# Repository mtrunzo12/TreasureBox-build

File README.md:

# Knock-to-Unlock Treasure Chest

Build a toy chest with a saved knock rhythm, keypad PIN, servo claw, lights and music. This folder is a curated snapshot of Mark and Liam's build. Start small: get the inputs working on a breadboard before ordering boards.

## Start here

1. Install [Claude Code](https://code.claude.com/docs/en/setup) or [Codex](https://developers.openai.com/codex/quickstart/), plus [Arduino IDE](https://www.arduino.cc/en/software/) and [KiCad](https://www.kicad.org/download/).
2. Download and unzip this build kit. Open the whole `treasure-chest` folder in your AI coding app. From [GitHub](https://github.com/mtrunzo12/TreasureBox-build), use Code → Download ZIP; no terminal or Git knowledge is required. Forking is optional and gives you your own place to save changes.
3. Paste the prompt from `START-HERE.md`. Ask the assistant to explain the next small step, then stop for your measurements or a photo. Do not ask it to order parts or fabricate a board before the checks below.

## What is included

- `firmware/treasure_box/`: current v8.5 sketch and its two required headers. Keep all three files in this folder.
- `firmware/USER_MANUAL.md`: using the toy and recording knock/PIN/music settings.
- `firmware/DEVELOPER.md`: exact pin map, dependencies, programming workflow and mechanical limits.
- `treasure_box_main/`: main-board schematic, layout, KiCad project and original exported BOM.
- `treasure_box_frontpanel/`: panel-board schematic, layout, KiCad project and original exported BOM.
- Each board folder includes the historical A0 Gerber/drill package and individual fabrication files.
- `PARTS.csv`: combined exported PCB component lists (44 placements across both boards). These are design values/footprints, not a verified supplier cart. The off-board parts are listed below.
- `KNOWN-ISSUES.md`: read this before spending money.
- `CHECKLIST.md`: a build sequence for a parent and child.
- `SOURCE-MANIFEST.json`: snapshot and source hashes. No family photographs, device backups, EEPROM dumps, credentials, local history or old build logs are included.

## Ordering the boards

This is the as-built A0 design, not a newly reviewed production release. The owner reports a backwards USB-C design; the build uses a removable ATmega328P programmed in a compatible DIP Uno. Resolve and review that issue before treating this as a plug-in USB design.

1. Open the `.kicad_pro` in each board folder. Check component orientation, connector pin numbering, footprint fit, board outline and hole locations against your parts and chest.
2. Run KiCad's electrical and PCB design-rule checks. Review their findings; a clean result alone does not prove the connector or physical wiring is correct.
3. Decide whether you are intentionally reproducing A0 with the Uno programming workaround or correcting the hardware first. If changed, regenerate Gerber and drill files from that exact saved revision. Do not order the historical ZIP for a revised board.
4. Upload **one ZIP per board** to JLCPCB. Confirm both copper layers, masks, silkscreen, board outline, drill holes and displayed dimensions in the preview. Use the [JLCPCB KiCad export guide](https://jlcpcb.com/help/article/how-to-generate-gerber-and-drill-files-in-kicad-9).
5. Choose bare PCB fabrication if you want to solder it yourselves. This package is not a turnkey assembly order; it does not include verified supplier part numbers or placement data. Check quantity, material, thickness and finish against the actual design before paying.
6. Check the delivered bare boards for obvious defects and shorts before populating them.

## Off-board parts to plan for

A wooden chest; piezo knock disc; reed switch and magnet; tilt switch; 4×4 keypad; passive speaker; illuminated arm button; red, green and blue lights with the appropriate wiring/resistors; four-AA holder and cells; main power switch; matching 16-way ribbon connectors/cable; keypad harness; wire, mounting hardware and strain relief. The installed claw is ServoCity 3219-0002-0002 with a goBILDA Proton Torque 2002-0180-0002 servo. Verify all electrical ratings and connector pitches before buying.

Tools: soldering iron, solder, ventilation, wire cutters/strippers, multimeter, breadboard/jumpers, and a compatible socketed ATmega328P Uno for the documented programming workaround. An adult handles soldering and initial powered claw tests. Keep fingers clear of the mechanism.

## Firmware

Open `firmware/treasure_box/treasure_box.ino` in Arduino IDE. The documented target is Arduino Uno / ATmega328P, Arduino AVR Boards 1.8.8 and Servo 1.3.0. Use the developer guide for the correct `BENCH_WIRING` choice; the custom PCB uses `false`, even when its removable chip is programmed in an Uno. Review the actual pin map before loading it onto a different breadboard arrangement.

An unprogrammed ATmega328P may need its bootloader and fuse configuration prepared first. Do not assume every purchased chip arrives Uno-ready. Power everything off before transferring a socketed chip, and check its notch orientation.

The code was built and tested on the original setup. Knock sensitivity, mechanical endpoints, wake behavior and battery draw still need testing on your own assembled chest. This is a toy latch, not a security lock.

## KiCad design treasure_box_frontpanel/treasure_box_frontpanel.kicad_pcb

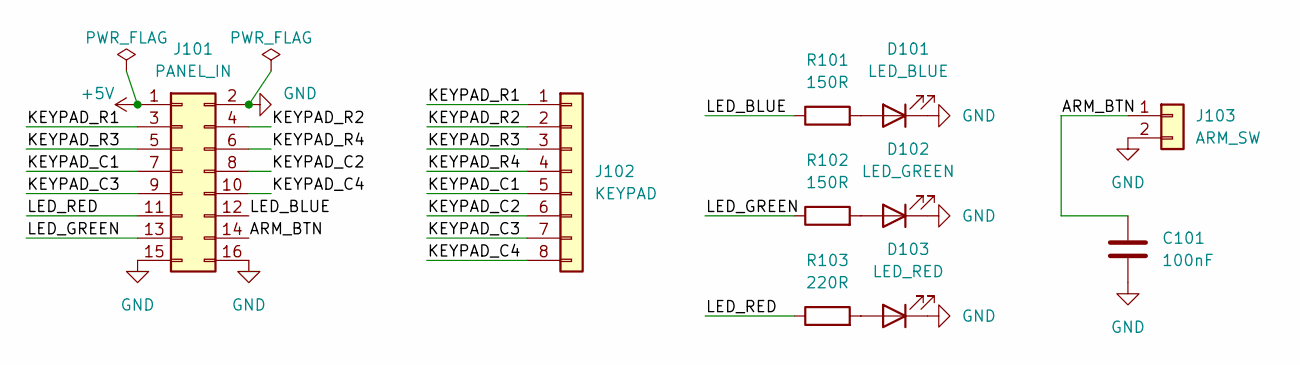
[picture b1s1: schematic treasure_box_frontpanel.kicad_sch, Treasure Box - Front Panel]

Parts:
C101: 100nF; C_Disc_D5.0mm_W2.5mm_P5.00mm
D101: LED_BLUE; TerminalBlock_MaiXu_MX126-5.0-02P_1x02_P5.00mm
D102: LED_GREEN; TerminalBlock_MaiXu_MX126-5.0-02P_1x02_P5.00mm
D103: LED_RED; TerminalBlock_MaiXu_MX126-5.0-02P_1x02_P5.00mm
J101: PANEL_IN; IDC-Header_2x08_P2.54mm_Vertical
J102: KEYPAD; JST_XH_B8B-XH-A_1x08_P2.50mm_Vertical
J103: ARM_SW; TerminalBlock_MaiXu_MX126-5.0-02P_1x02_P5.00mm
R101, R102: 150R; R_Axial_DIN0207_L6.3mm_D2.5mm_P10.16mm_Horizontal
R103: 220R; R_Axial_DIN0207_L6.3mm_D2.5mm_P10.16mm_Horizontal

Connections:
+5V: J101.1
/ARM_BTN: C101.1, J101.14, J103.1
/KEYPAD_C1: J101.7, J102.5
/KEYPAD_C2: J101.8, J102.6
/KEYPAD_C3: J101.9, J102.7
/KEYPAD_C4: J101.10, J102.8
/KEYPAD_R1: J101.3, J102.1
/KEYPAD_R2: J101.4, J102.2
/KEYPAD_R3: J101.5, J102.3
/KEYPAD_R4: J101.6, J102.4
/LED_BLUE: J101.12, R101.1
/LED_GREEN: J101.13, R102.1
/LED_RED: J101.11, R103.1
GND: C101.2, D101.1 (K), D102.1 (K), D103.1 (K), J101.2, J101.15, J101.16, J103.2
unnamed: D101.2 (A), R101.2
unnamed: D102.2 (A), R102.2
unnamed: D103.2 (A), R103.2

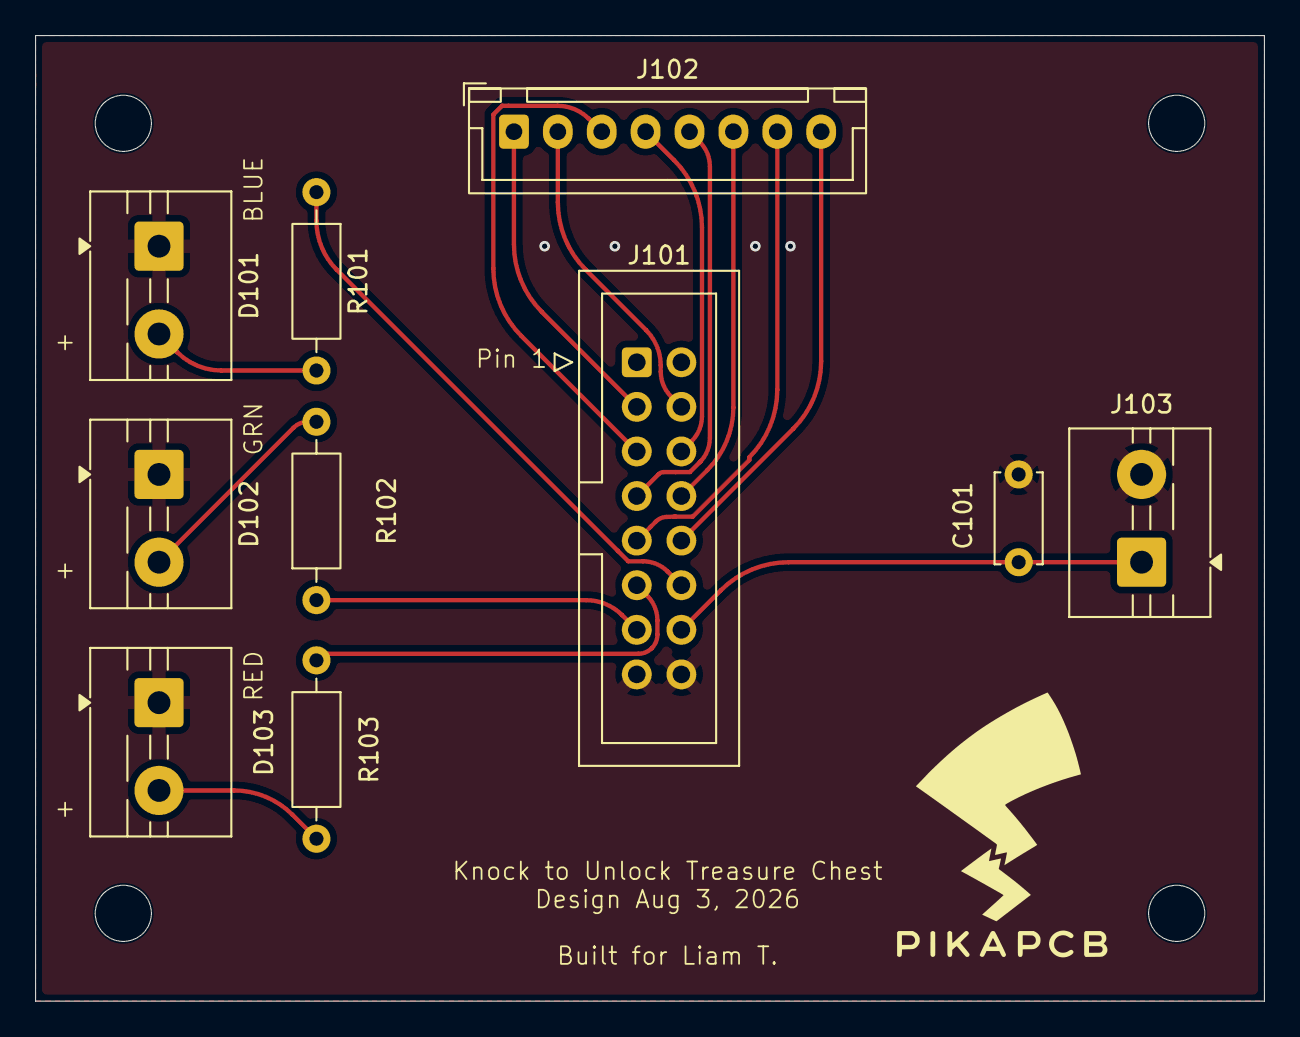
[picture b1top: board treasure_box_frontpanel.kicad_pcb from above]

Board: 2 copper layers, 70.0 x 55.0 mm, 15 parts (0 on the bottom side), 16 nets.

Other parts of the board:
Mount: MountingHole_3.2mm_M3
Mount#2, Mount#3, Mount#4: MountingHole_3.2mm_M3
P: LOGO; PikaPCBsmall

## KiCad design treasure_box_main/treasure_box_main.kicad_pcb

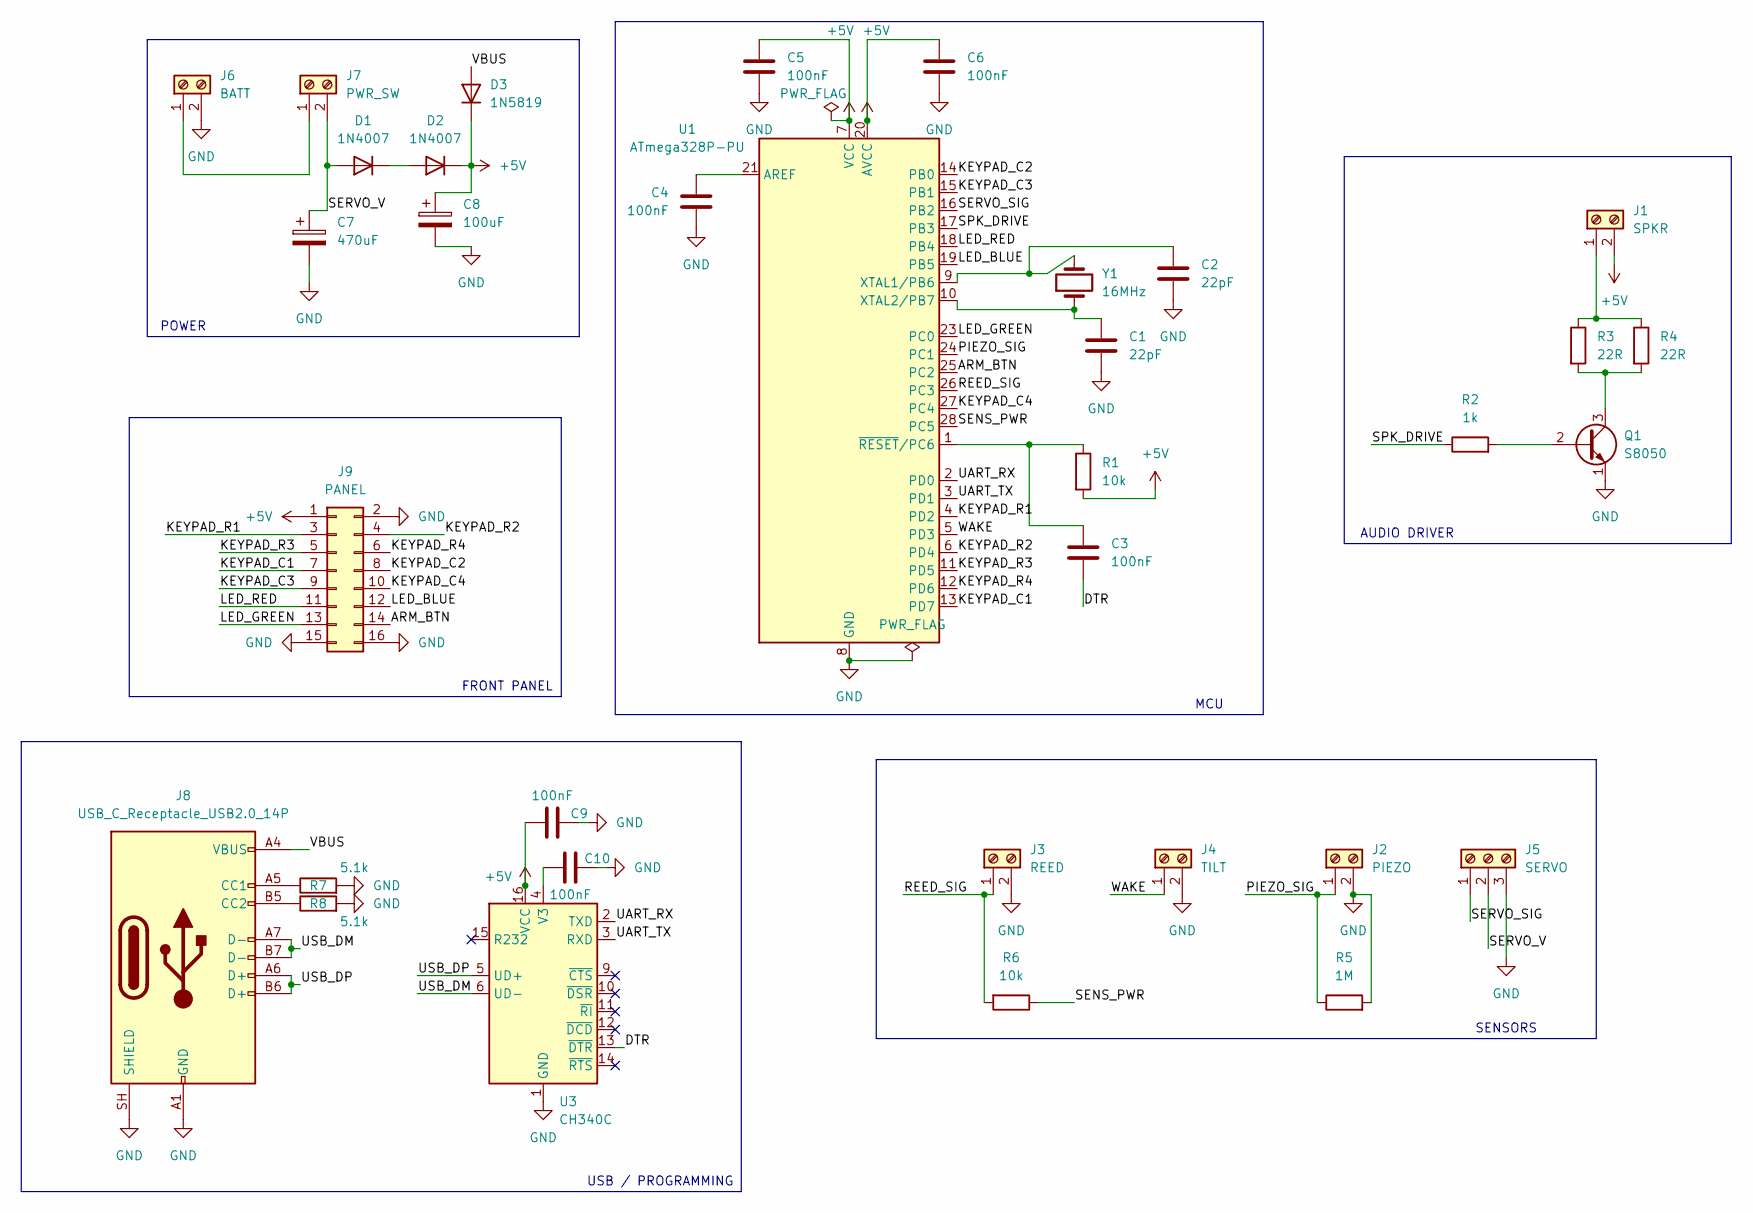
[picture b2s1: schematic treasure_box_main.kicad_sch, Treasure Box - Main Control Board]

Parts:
C1, C2: 22pF; C_Disc_D3.0mm_W1.6mm_P2.50mm
C3, C4, C5, C6, C9, C10: 100nF; C_Disc_D3.0mm_W1.6mm_P2.50mm
C7: 470uF; CP_Radial_D8.0mm_P3.50mm
C8: 100uF; CP_Radial_D6.3mm_P2.50mm
D1, D2: 1N4007; D_DO-41_SOD81_P10.16mm_Horizontal
D3: 1N5819; D_DO-41_SOD81_P10.16mm_Horizontal
J1: SPKR; TerminalBlock_MaiXu_MX126-5.0-02P_1x02_P5.00mm
J2: PIEZO; TerminalBlock_MaiXu_MX126-5.0-02P_1x02_P5.00mm
J3: REED; TerminalBlock_MaiXu_MX126-5.0-02P_1x02_P5.00mm
J4: TILT; TerminalBlock_MaiXu_MX126-5.0-02P_1x02_P5.00mm
J5: SERVO; TerminalBlock_MaiXu_MX126-5.0-03P_1x03_P5.00mm
J6: BATT; TerminalBlock_MaiXu_MX126-5.0-02P_1x02_P5.00mm
J7: PWR_SW; TerminalBlock_MaiXu_MX126-5.0-02P_1x02_P5.00mm
J8: USB_C_Receptacle_USB2.0_14P; USB_C_Receptacle_HRO_TYPE-C-31-M-12
J9: PANEL; IDC-Header_2x08_P2.54mm_Vertical
Q1: S8050; TO-92_Inline
R1, R6: 10k; R_Axial_DIN0207_L6.3mm_D2.5mm_P10.16mm_Horizontal
R2: 1k; R_Axial_DIN0207_L6.3mm_D2.5mm_P10.16mm_Horizontal
R3, R4: 22R; R_Axial_DIN0207_L6.3mm_D2.5mm_P10.16mm_Horizontal
R5: 1M; R_Axial_DIN0207_L6.3mm_D2.5mm_P10.16mm_Horizontal
R7, R8: 5.1k; R_Axial_DIN0207_L6.3mm_D2.5mm_P10.16mm_Horizontal
U1: ATmega328P-PU; DIP-28_W7.62mm_Socket
U3: CH340C; SOIC-16_3.9x9.9mm_P1.27mm
Y1: 16MHz; Crystal_HC49-4H_Vertical

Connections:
+5V: C5.1, C6.1, C8.1, C9.1, D2.1 (K), D3.1 (K), J1.2, J9.1, R1.2, U1.7 (VCC), U1.20 (AVCC), U3.16 (VCC)
/ARM_BTN: J9.14, U1.25 (PC2)
/DTR: C3.2, U3.13 (~DTR)
/KEYPAD_C1: J9.7, U1.13 (PD7)
/KEYPAD_C2: J9.8, U1.14 (PB0)
/KEYPAD_C3: J9.9, U1.15 (PB1)
/KEYPAD_C4: J9.10, U1.27 (PC4)
/KEYPAD_R1: J9.3, U1.4 (PD2)
/KEYPAD_R2: J9.4, U1.6 (PD4)
/KEYPAD_R3: J9.5, U1.11 (PD5)
/KEYPAD_R4: J9.6, U1.12 (PD6)
/LED_BLUE: J9.12, U1.19 (PB5)
/LED_GREEN: J9.13, U1.23 (PC0)
/LED_RED: J9.11, U1.18 (PB4)
/PIEZO_SIG: J2.1, R5.1, U1.24 (PC1)
/REED_SIG: J3.1, R6.2, U1.26 (PC3)
/SENS_PWR: R6.1, U1.28 (PC5)
/SERVO_SIG: J5.1, U1.16 (PB2)
/SERVO_V: C7.1, D1.2 (A), J5.2, J7.2
/SPK_DRIVE: R2.1, U1.17 (PB3)
/UART_RX: U1.2 (PD0), U3.2 (TXD)
/UART_TX: U1.3 (PD1), U3.3 (RXD)
/USB_DM: J8.A7 (D-), J8.B7 (D-), U3.6 (UD-)
/USB_DP: J8.A6 (D+), J8.B6 (D+), U3.5 (UD+)
/VBUS: D3.2 (A), J8.A4 (VBUS), J8.A9 (VBUS), J8.B4 (VBUS), J8.B9 (VBUS)
/WAKE: J4.1, U1.5 (PD3)
GND: C1.2, C2.2, C4.2, C5.2, C6.2, C7.2, C8.2, C9.2, C10.2, J2.2, J3.2, J4.2, J5.3, J6.2, J8.A1 (GND), J8.A12 (GND), J8.B1 (GND), J8.B12 (GND), J8.SH (SHIELD), J9.2, J9.15, J9.16, Q1.1 (E), R5.2, R7.2, R8.2, U1.8 (GND), U1.22 (GND), U3.1 (GND)
unnamed: D1.1 (K), D2.2 (A)
unnamed: J1.1, R3.1, R4.1
unnamed: J6.1, J7.1
unnamed: J8.A5 (CC1), R7.1
unnamed: J8.B5 (CC2), R8.1
unnamed: Q1.2 (B), R2.2
unnamed: Q1.3 (C), R3.2, R4.2
unnamed: C4.1, U1.21 (AREF)
unnamed: C2.1, U1.9 (XTAL1/PB6), Y1.2
unnamed: C1.1, U1.10 (XTAL2/PB7), Y1.1
unnamed: C3.1, R1.1, U1.1 (~RESET/PC6)
unnamed: C10.1, U3.4 (V3)

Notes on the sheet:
FRONT PANEL
SENSORS
AUDIO DRIVER
POWER
USB / PROGRAMMING
MCU

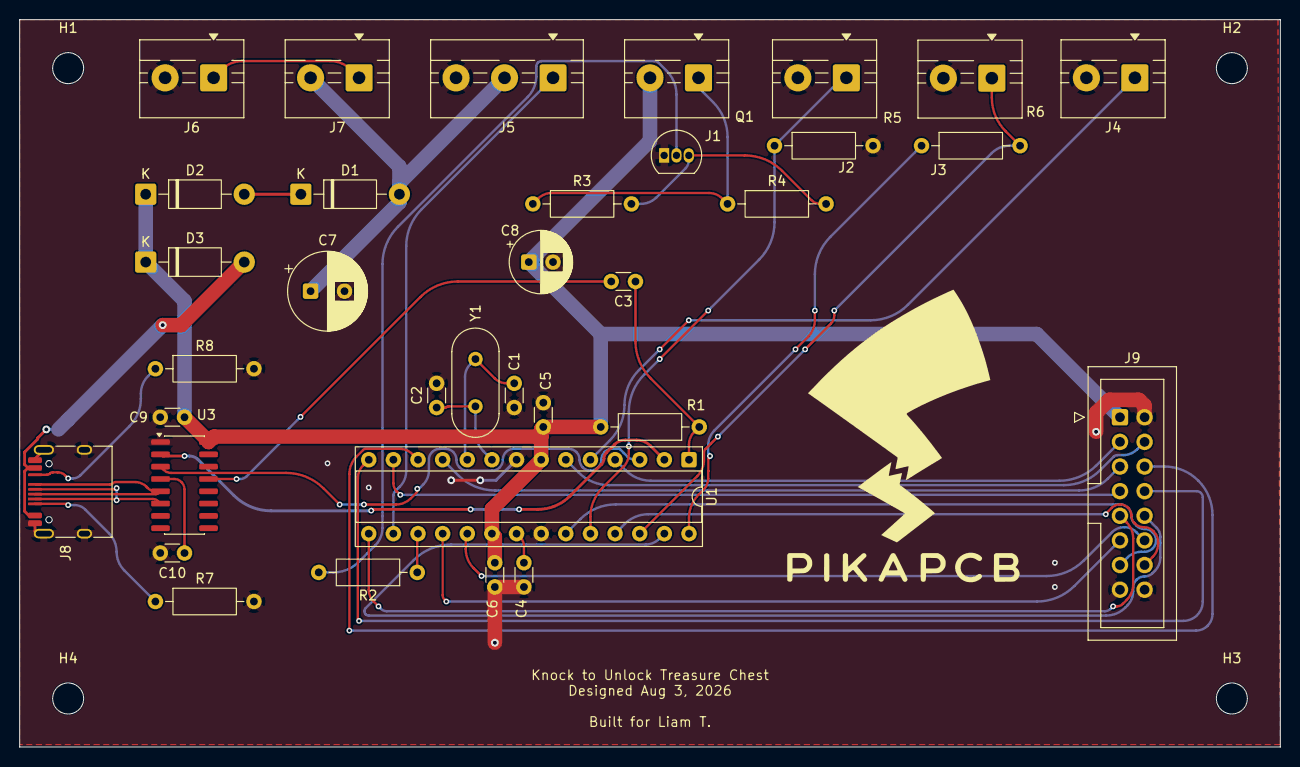
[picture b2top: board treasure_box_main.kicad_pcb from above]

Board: 2 copper layers, 130.0 x 75.0 mm, 38 parts (0 on the bottom side), 39 nets.

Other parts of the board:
H1, H2, H3, H4: MountingHole_3.2mm_M3
